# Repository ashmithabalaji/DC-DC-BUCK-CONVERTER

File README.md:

View this project on [CADLAB.io](https://cadlab.io/project/29252). 

# DC-DC-BUCK-CONVERTER

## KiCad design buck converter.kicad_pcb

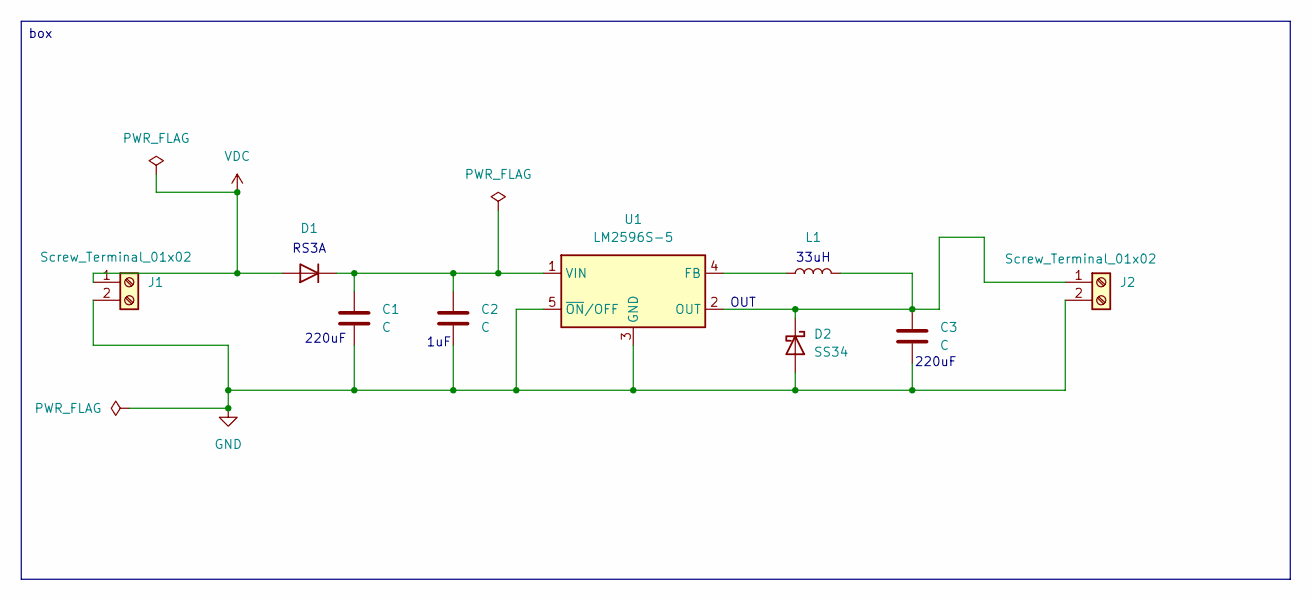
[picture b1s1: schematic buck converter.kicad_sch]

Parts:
C1, C2, C3: C; CP_Radial_D5.0mm_P2.00mm
D1: D; D_DO-201AD_P15.24mm_Horizontal
D2: SS34; D_SMA
J1, J2: Screw_Terminal_01x02; TerminalBlock_bornier-2_P5.08mm
L1: L; L_Radial_D10.0mm_P5.00mm_Fastron_07M
U1: LM2596S-5; TO-263-5_TabPin3

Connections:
GND: C1.2, C2.2, C3.2, D2.2 (A), J1.2, J2.2, U1.3 (GND), U1.5 (~ON/OFF)
unnamed: C1.1, C2.1, D1.1 (K), U1.1 (VIN)
unnamed: C3.1, D2.1 (K), J2.1, L1.2, U1.2 (OUT)
unnamed: L1.1, U1.4 (FB)
VDC: D1.2 (A), J1.1

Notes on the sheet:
OUT
1uF
220uF
33uH
RS3A
box

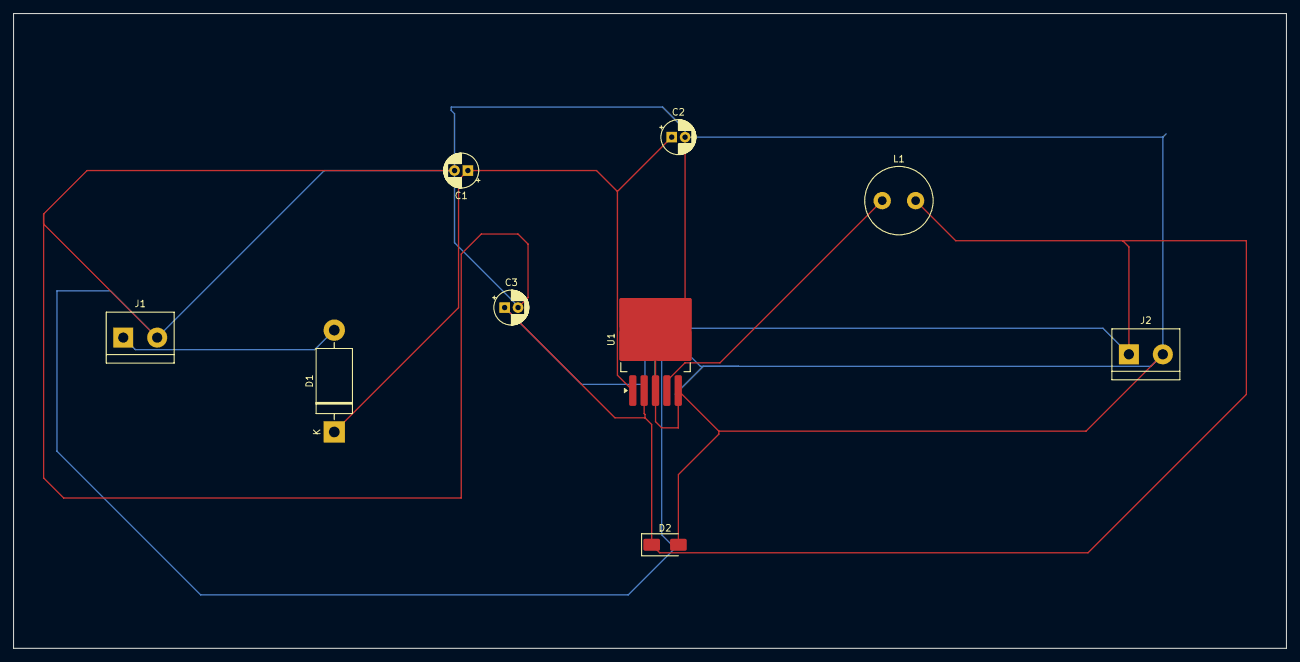
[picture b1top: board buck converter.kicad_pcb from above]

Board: 2 copper layers, 190.5 x 95.0 mm, 9 parts (0 on the bottom side), 5 nets.

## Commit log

2025-04-11 Backlink to CADLAB.io has been added.
